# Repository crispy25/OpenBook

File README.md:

# OpenBook - TSC Project
### Author: Popescu Cristian-Emanuel 332CA

## Diagram

## Hardware functionality

+ ESP32-C6 MCU
    - Manages all peripherals, including the display, sensors, buttons, and USB-C interface.
    - Interfaces: SPI, I2C, USB, UART, Wi-Fi

+ Power Supply - CELLEVIA BATTERIES LP584174
    - The 1800mAh Polymer Lithium-Ion battery is connected to the charging IC.
    - A single LDO generates the required single 3.3V power rail for the entire board, powering the ESP32, sensors and other components.

+ Battery management - MAX17048G+T10
    - The battery management module is using the I2C interface to communicate with the battery fuel gauge IC.
    - The charging IC is controlled via GPIO pins.

+ Display Interface - Waveshare WSH-13187 7.5" e-Paper display 
    - The 800x480 resolution display is connected to the ESP32-C6 via a 4-wire SPI interface.
    - Dedicated CS, DC, RST, and BUSY pins are used for control.

+ Sensor - Bosch BME680
    - Measures temperature, humidity, pressure and air quality.
    - The BME680 sensor is connected to the ESP32-C6 via an I2C bus.
    - Pull-up resistors are used on the I2C lines.

+ RTC - DS3231
    - Real Time Clock with supercapacitor back-up.
    - Connected via I2C interface.

+ User Interface
    - The three tactile buttons are connected to GPIO pins on the ESP32-C6.
    - Hardware debouncing circuitry is implemented using RC filters.
    - The RESET button restarts the device, typically used to recover from unresponsive states or system errors.
    - The BOOT button allows the user to start up the device.
    - The CHANGE button lets the user scroll or cycle through menus and book selections.

+ External NOR Flash 64MB - W25Q512JVEIQ
    - Non-Volatile flash memory that provides a storage solution.
    - Interface: SPI

+ USB-C Interface
    - The USB-C connector is connected to the ESP32-C6's USB interface.
    - A dedicated ESD protection IC is used on the data and power lines.
    - Proper termination resistors are used for USB-C implementation.

+ SD Memory Card Connector - Attend Tech 112A-TAAR-R03
    - Interface: SPI

+ Qwiic / Stemma QT
    - Plug-and-play I2C connection system for easy expansion of peripheral modules.

## Power management and consumption

| Mode       | ESP32  | EPD  | BME680    | DS3231  | MAX17048 | SD Card | Total Current | Runtime       |
|------------|--------|------|-----------|---------|----------|---------|---------------|:-------------:|
| Active     | 100mA  | 30mA | 2mA       | 0.2mA   | 0.05mA   | 80mA    | ~212 mA       | ~8.5 hours    |
| Idle       | 50mA   | 1µA  | 150µA     | 0.2mA   | 0.05mA   | 2mA     | ~52.4 mA      | ~1.4 days     |
| Deep Sleep | 0.15mA | 1µA  | 0.00015mA | 0.003mA | 0.001mA  | 0.1mA   | ~0.255 mA     | ~9.7 months   |

## ESP32-C6 Pin description

+ EN -> Resets the MCU
+ IO0 - INT_RTC -> Used to receive interrupts signals from RTC, allowing for two major functionalities: Alarm and Square Wave Output
+ IO1 - 32KHz -> Used for a stable clock signal of 32.768 kHz generated by the RTC
+ IO2 – MISO -> Master In Slave Out Signal, used in the SPI communication with the SD Card
+ IO3 - EPD_BUSY -> Indicates display driver status
+ IO4 – SS_SD -> Chip select for SPI communication with SD Card
+ IO5 – EPD_DC -> Display serial communication Command/Data input
+ IO6 – SCK -> Clock signal for I2C communication
+ IO7 – MOSI -> Master Out Slave In Signal, used to send data to display and SD Card
+ IO8 - GPIO8 - Controls MCU boot mode
+ IO9 - IO/BOOT -> Used to detect BOOT button press
+ NC -> Not connected
+ 3V3 -> Used to power the MCU and the other components
+ IO10 - EPD_CS -> Chip select for SPI serial communication with the display
+ IO11 - FLASH_CS -> Chip select for SPI communication with the flash
+ IO12 - USB_D- -> Used in USB differential communication
+ IO13 - USB_D+ -> Used in USB differential communication
+ IO15 - IO/CHANGE -> Used to detect CHANGE button press
+ TXD0/GPIO16 - TX -> Sends data to another device via UART
+ RXD0/GPIO17 - RX -> Receives data from another device via UART
+ IO18 - RTC_RST -> Resets the RTC
+ IO19 - I2C_PW -> Power source for I2C components
+ IO20 - EPD_3V3_C -> Display IO voltage supply
+ IO21 - SDA -> Used to send and receive data in the I2C communication with the sensor, RTC module and Battery Fuel Gauge
+ IO22 - SCL -> Clock signal for I2C communication
+ IO23 - EPD_RST -> Global reset signal for the display
+ GND -> Shared Voltage Reference

## Bill of Materials:
|                                                                                                         |                                                                                |     |                                                                                                                                                                                                                                                                                                                                                                                                                                                                                                                                                                                                                  |                                                                                                                                                                                                                |
| ------------------------------------------------------------------------------------------------------- | ------------------------------------------------------------------------------ | --- | ---------------------------------------------------------------------------------------------------------------------------------------------------------------------------------------------------------------------------------------------------------------------------------------------------------------------------------------------------------------------------------------------------------------------------------------------------------------------------------------------------------------------------------------------------------------------------------------------------------------- | -------------------------------------------------------------------------------------------------------------------------------------------------------------------------------------------------------------- |
| Parts                                                                                                   | Value                                                                          | Qty | CHECK_PRICES                                                                                                                                                                                                                                                                                                                                                                                                                                                                                                                                                                                                     | DATASHEET                                                                                                                                                                                                      |
| CHG_LED                                                                                                 |                                                                                | 1   | [https://ro.mouser.com/ProductDetail/ams-OSRAM/KO-EELP41.22-Q1S2-25-A8J8-020-R18?qs=ZcfC38r4PoswH9uD%2FZTNyw%3D%3D](https://ro.mouser.com/ProductDetail/ams-OSRAM/KO-EELP41.22-Q1S2-25-A8J8-020-R18?qs=ZcfC38r4PoswH9uD%2FZTNyw%3D%3D)                                                                                                                                                                                                                                                                                                                                                                           | [https://www.farnell.com/datasheets/4386964.pdf](https://www.farnell.com/datasheets/4386964.pdf)                                                                                                               |
| SJ1                                                                                                     |                                                                                | 1   | [https://ro.mouser.com/ProductDetail/ROHM-Semiconductor/PMR01ZZPJ000?qs=jQ44l%2F%2F3jsmEdW2XxNXnVw%3D%3D](https://ro.mouser.com/ProductDetail/ROHM-Semiconductor/PMR01ZZPJ000?qs=jQ44l%2F%2F3jsmEdW2XxNXnVw%3D%3D)                                                                                                                                                                                                                                                                                                                                                                                               | [https://fscdn.rohm.com/en/products/databook/datasheet/passive/resistor/chip_resistor/pmr_series-e.pdf](https://fscdn.rohm.com/en/products/databook/datasheet/passive/resistor/chip_resistor/pmr_series-e.pdf) |
| C7                                                                                                      | 10uF                                                                          | 1   | [https://ro.mouser.com/ProductDetail/KYOCERA-AVX/CM05X5R106M10AH?qs=MyNHzdoqoQKSCgSEDR5Ylg%3D%3D](https://ro.mouser.com/ProductDetail/KYOCERA-AVX/CM05X5R106M10AH?qs=MyNHzdoqoQKSCgSEDR5Ylg%3D%3D)                                                                                                                                                                                                                                                                                                                                                                                                               | [https://ro.mouser.com/datasheet/2/40/CM_Series_e-2835982.pdf](https://ro.mouser.com/datasheet/2/40/CM_Series_e-2835982.pdf)                                                                                   |
| EPD_C5                                                                                                  | 0.1uF/50V                                                                      | 1   | [04025C104JAT2A KYOCERA AVX \| Mouser Romania](https://ro.mouser.com/ProductDetail/KYOCERA-AVX/04025C104JAT2A?qs=yqaQSyyJnNjAUYBPnTRwrw%3D%3D)                                                                                                                                                                                                                                                                                                                                                                                                                                                                   | [https://ro.mouser.com/datasheet/2/40/AutoMLCC-2952695.pdf](https://ro.mouser.com/datasheet/2/40/AutoMLCC-2952695.pdf)                                                                                         |
| R3                                                                                                      | 0.47                                                                           | 1   | [https://ro.mouser.com/ProductDetail/Vishay-Dale/RCWE0402R470FKEA?qs=sGAEpiMZZMvdGkrng054t3yNvgEjAsaw5ZqUmX9fhQU%3D](https://ro.mouser.com/ProductDetail/Vishay-Dale/RCWE0402R470FKEA?qs=sGAEpiMZZMvdGkrng054t3yNvgEjAsaw5ZqUmX9fhQU%3D)                                                                                                                                                                                                                                                                                                                                                                         | [rcwe.pdf](https://www.vishay.com/docs/20019/rcwe.pdf)                                                                                                                                                         |
| R1_PWRUSB                                                                                               | 100K                                                                           | 1   | [MCS0402MD1003BE000 Vishay / Beyschlag \| Mouser Romania](https://ro.mouser.com/ProductDetail/Vishay-Beyschlag/MCS0402MD1003BE000?qs=sGAEpiMZZMvdGkrng054t2cqbZCzJY7NbpFPWPjr8LU6rj01EMMGYg%3D%3D)                                                                                                                                                                                                                                                                                                                                                                                                               | [mcs0402at-mct0603at-mcu0805at-mca1206at.pdf](https://www.vishay.com/docs/28952/mcs0402at-mct0603at-mcu0805at-mca1206at.pdf)                                                                                   |
| C1, C2, C4_USB, C6, C8, C9, C10, C_DELAY                                                                | 100nF                                                                          | 8   | [0402YC104MAT2A KYOCERA AVX \| Mouser Romania](https://ro.mouser.com/ProductDetail/KYOCERA-AVX/0402YC104MAT2A?qs=O2%2FeDh0sX9yiCaLwpXy1bw%3D%3D)                                                                                                                                                                                                                                                                                                                                                                                                                                                                 | [https://ro.mouser.com/datasheet/2/40/KGM_X7R-3223212.pdf](https://ro.mouser.com/datasheet/2/40/KGM_X7R-3223212.pdf)                                                                                           |
| C3                                                                                                      | 100uF                                                                          | 1   | [F910J107MBAAJ6 KYOCERA AVX \| Mouser Romania](https://ro.mouser.com/ProductDetail/KYOCERA-AVX/F910J107MBAAJ6?qs=PqoDHHvF649LraCA%2FjeGXg%3D%3D)                                                                                                                                                                                                                                                                                                                                                                                                                                                                 | https://ro.mouser.com/datasheet/2/40/F91_AJ6-3162641.pdf                                                                                                                                                       |
| R1, R1_PINH, R1_PINH1, R2-PINH, R2-PINH1, R4, R5, R6, R7, R8, R9, R10, R_BOOT, R_CHANGE, R_CL1, R_RESET | 10K                                                                            | 16  | [CRCW040210K0FKEDC Vishay / Dale \| Mouser Romania](https://ro.mouser.com/ProductDetail/Vishay-Dale/CRCW040210K0FKEDC?qs=sGAEpiMZZMvdGkrng054t0DrEhLhGh8ghRTPC4LoFoV0V5heIyAs3Q%3D%3D)                                                                                                                                                                                                                                                                                                                                                                                                                           | [crcwce3.pdf](https://www.vishay.com/docs/28773/crcwce3.pdf)                                                                                                                                                   |
| J4                                                                                                      | 112A-TAAR-R03_ATTEND                                                           | 1   | [https://store.comet.srl.ro/Catalogue/Product/43497/](https://store.comet.srl.ro/Catalogue/Product/43497/)                                                                                                                                                                                                                                                                                                                                                                                                                                                                                                       | [https://www.attend.com.tw/data/download/file/112A-TAAR-R03_Spec.pdf](https://www.attend.com.tw/data/download/file/112A-TAAR-R03_Spec.pdf)                                                                     |
| R_CAPACITOR                                                                                             | 15                                                                             | 1   | [https://ro.mouser.com/ProductDetail/Vishay-Dale/CRCW040215R0FKEDC?qs=sGAEpiMZZMvdGkrng054t0DrEhLhGh8gIyCo%252BhYIiOaNlcXwcpoKSQ%3D%3D](https://ro.mouser.com/ProductDetail/Vishay-Dale/CRCW040215R0FKEDC?qs=sGAEpiMZZMvdGkrng054t0DrEhLhGh8gIyCo%252BhYIiOaNlcXwcpoKSQ%3D%3D)                                                                                                                                                                                                                                                                                                                                   | [crcwce3.pdf](https://www.vishay.com/docs/28773/crcwce3.pdf)                                                                                                                                                   |
| C5                                                                                                      | 1uF                                                                            | 1   | [0402YC104MAT2A KYOCERA AVX \| Mouser Romania](https://ro.mouser.com/ProductDetail/KYOCERA-AVX/0402YC104MAT2A?qs=O2%2FeDh0sX9yiCaLwpXy1bw%3D%3D)                                                                                                                                                                                                                                                                                                                                                                                                                                                                 | [https://ro.mouser.com/datasheet/2/40/KGM_X7R-3223212.pdf](https://ro.mouser.com/datasheet/2/40/KGM_X7R-3223212.pdf)                                                                                           |
| EPD_C1, EPD_C2, EPD_C6, EPD_C7, EPD_C8, EPD_C9, EPD_C10, EPD_C11, EPD_C12                               | 1uF/50V                                                                        | 9   | [GRM155R61H105KE05D Murata Electronics \| Mouser Romania](https://ro.mouser.com/ProductDetail/Murata-Electronics/GRM155R61H105KE05D?qs=d0WKAl%252BL4KazJ%252BOnevMfYg%3D%3D)                                                                                                                                                                                                                                                                                                                                                                                                                                     | [GRM155R61H105KE05_01A-1983895.pdf](https://ro.mouser.com/datasheet/2/281/1/GRM155R61H105KE05_01A-1983895.pdf)                                                                                                 |
| R2                                                                                                      | 2.2                                                                            | 1   | [CRCW04022R20JNEDHP Vishay / Dale \| Mouser Romania](https://ro.mouser.com/ProductDetail/Vishay-Dale/CRCW04022R20JNEDHP?qs=sGAEpiMZZMvdGkrng054tyhjHjtogURyZ4iA06yjwtU%3D)                                                                                                                                                                                                                                                                                                                                                                                                                                       | [https://www.vishay.com/docs/20043/crcwhpe3.pdf](https://www.vishay.com/docs/20043/crcwhpe3.pdf)                                                                                                               |
| R1_BAT                                                                                                  | 200                                                                            | 1   | [CRCW0402200RJNEDHP Vishay / Dale \| Mouser Romania](https://ro.mouser.com/ProductDetail/Vishay-Dale/CRCW0402200RJNEDHP?qs=sGAEpiMZZMvdGkrng054t7z4BkURc4Lz9xM5ulmOcXZJ7C0YzNP%252BSg%3D%3D)                                                                                                                                                                                                                                                                                                                                                                                                                     | [crcwhpe3.pdf](https://www.vishay.com/docs/20043/crcwhpe3.pdf)                                                                                                                                                 |
| Q1, Q2                                                                                                  | 20V/4.2A/52mO/1.4W                                                             | 2   | [https://ro.mouser.com/ProductDetail/Diodes-Incorporated/DMG2305UX-7?qs=L1DZKBg7t5F%2FNBHrjfxC%252Bg%3D%3D](https://ro.mouser.com/ProductDetail/Diodes-Incorporated/DMG2305UX-7?qs=L1DZKBg7t5F%2FNBHrjfxC%252Bg%3D%3D)                                                                                                                                                                                                                                                                                                                                                                                           | [DMG2305UX](https://www.diodes.com/assets/Datasheets/DMG2305UX.pdf)                                                                                                                                            |
| R2_BAT                                                                                                  | 2K                                                                             | 1   | [MCS0402PD2001DE500 Vishay / Beyschlag \| Mouser Romania](https://ro.mouser.com/ProductDetail/Vishay-Beyschlag/MCS0402PD2001DE500?qs=sGAEpiMZZMvdGkrng054t7z4BkURc4Lz%2FlDTCWzmnHsTHTkVY59%252BKw%3D%3D)                                                                                                                                                                                                                                                                                                                                                                                                         | [https://www.vishay.com/docs/28916/mcxhp.pdf](https://www.vishay.com/docs/28916/mcxhp.pdf)                                                                                                                     |
| C1_BAT, C1_BAT1, C1_BAT2, C2_BAT, C5_USB                                                                | 4.7uF                                                                          | 5   | [CM05X5R475M25AH KYOCERA AVX \| Mouser Romania](https://ro.mouser.com/ProductDetail/KYOCERA-AVX/CM05X5R475M25AH?qs=MyNHzdoqoQJvFdZaEuclBg%3D%3D)                                                                                                                                                                                                                                                                                                                                                                                                                                                                 | https://ro.mouser.com/datasheet/2/40/CM_Series_e-2835982.pdf                                                                                                                                                   |
| C4                                                                                                      | 4.7uF/25V                                                                      | 1   | [CM05X5R475M25AH KYOCERA AVX \| Mouser Romania](https://ro.mouser.com/ProductDetail/KYOCERA-AVX/CM05X5R475M25AH?qs=MyNHzdoqoQJvFdZaEuclBg%3D%3D)                                                                                                                                                                                                                                                                                                                                                                                                                                                                 | https://ro.mouser.com/datasheet/2/40/CM_Series_e-2835982.pdf                                                                                                                                                   |
| R2-USB, R2-USB1                                                                                         | 5k1                                                                            | 2   | [https://ro.mouser.com/ProductDetail/Vishay-Beyschlag/MCS04020C5101FE000?qs=sGAEpiMZZMvdGkrng054t4QdAY%2FQ0LweI%252Blr2dxb1tw%3D](https://ro.mouser.com/ProductDetail/Vishay-Beyschlag/MCS04020C5101FE000?qs=sGAEpiMZZMvdGkrng054t4QdAY%2FQ0LweI%252Blr2dxb1tw%3D)                                                                                                                                                                                                                                                                                                                                               | [mcx0x0xpro.pdf](https://www.vishay.com/docs/28705/mcx0x0xpro.pdf)                                                                                                                                             |
| L1                                                                                                      | 68uH                                                                           | 1   | [https://ro.mouser.com/ProductDetail/Wurth-Elektronik/744043680?qs=PGXP4M47uW6VkZq%252BkzjrHA%3D%3D](https://ro.mouser.com/ProductDetail/Wurth-Elektronik/744043680?qs=PGXP4M47uW6VkZq%252BkzjrHA%3D%3D)                                                                                                                                                                                                                                                                                                                                                                                                         | [744043680 Datasheet WE-TPC SMT Shielded Tiny Power Inductor](https://www.we-online.com/components/products/datasheet/744043680.pdf)                                                                           |
| IC1                                                                                                     | BD5229G-TR                                                                     | 1   | [https://ro.mouser.com/ProductDetail/ROHM-Semiconductor/BD5229G-TR?qs=4kLU8WoGk0vvnhrrYwdszw%3D%3D](https://ro.mouser.com/ProductDetail/ROHM-Semiconductor/BD5229G-TR?qs=4kLU8WoGk0vvnhrrYwdszw%3D%3D)                                                                                                                                                                                                                                                                                                                                                                                                           | [BD52xx Series / BD53xx Series : Power Management](https://fscdn.rohm.com/en/products/databook/datasheet/ic/power/voltage_detector/bd52xxg-e.pdf)                                                              |
| BOOT_BUTTON, CHANGE_BUTTON, RESET_BUTTON                                                                | BUTTON_CUSYOMV1                                                                | 3   | [https://ro.mouser.com/ProductDetail/Panasonic/EVQ-P7L01P?qs=rJ%252BziJWpyszWhhNszc02jQ%3D%3D](https://ro.mouser.com/ProductDetail/Panasonic/EVQ-P7L01P?qs=rJ%252BziJWpyszWhhNszc02jQ%3D%3D)                                                                                                                                                                                                                                                                                                                                                                                                                     | [https://api.pim.na.industrial.panasonic.com/file_stream/main/fileversion/245500](https://api.pim.na.industrial.panasonic.com/file_stream/main/fileversion/245500)                                             |
| C10_SUPERCAP                                                                                            | CPH3225A                                                                       | 1   | [https://ro.mouser.com/ProductDetail/Seiko-Semiconductors/CPH3225A?qs=3etwrb1wR%252BhUOph6lAO7eg%3D%3D](https://ro.mouser.com/ProductDetail/Seiko-Semiconductors/CPH3225A?qs=3etwrb1wR%252BhUOph6lAO7eg%3D%3D)                                                                                                                                                                                                                                                                                                                                                                                                   | [https://ro.mouser.com/datasheet/2/360/Seiko_Instruments_MicroBattery_E_20230330_2024Jan_-3561061.pdf](https://ro.mouser.com/datasheet/2/360/Seiko_Instruments_MicroBattery_E_20230330_2024Jan_-3561061.pdf)   |
| U3                                                                                                      | DS3231SN#                                                                      | 1   | [https://ro.mouser.com/ProductDetail/Analog-Devices-Maxim-Integrated/DS3231SN?qs=1eQvB6Dk1vhUlr8%2FOrV0Fw%3D%3D](https://ro.mouser.com/ProductDetail/Analog-Devices-Maxim-Integrated/DS3231SN?qs=1eQvB6Dk1vhUlr8%2FOrV0Fw%3D%3D)                                                                                                                                                                                                                                                                                                                                                                                 | [DS3231-3421123.pdf](https://ro.mouser.com/datasheet/2/609/DS3231-3421123.pdf)                                                                                                                                 |
| U2                                                                                                      | ESP32-C6-WROOM-1-N8                                                            | 1   | [https://ro.mouser.com/ProductDetail/Espressif-Systems/ESP32-C6-WROOM-1-N8?qs=8Wlm6%252BaMh8ST02Gmwp74cw%3D%3D](https://ro.mouser.com/ProductDetail/Espressif-Systems/ESP32-C6-WROOM-1-N8?qs=8Wlm6%252BaMh8ST02Gmwp74cw%3D%3D)                                                                                                                                                                                                                                                                                                                                                                                   | [Espressif_ESP32_C6_WROOM_1__Datasheet_V0_1_PRELIMI-3239987.pdf](https://ro.mouser.com/datasheet/2/891/Espressif_ESP32_C6_WROOM_1__Datasheet_V0_1_PRELIMI-3239987.pdf)                                         |
| PFMF.050.1                                                                                              | ESP32C6_VARISTORCN1812                                                         | 1   | [https://ro.mouser.com/ProductDetail/Bourns/BVR1812-04R?qs=mELouGlnn3dev%2FRLzuGBiQ%3D%3D](https://ro.mouser.com/ProductDetail/Bourns/BVR1812-04R?qs=mELouGlnn3dev%2FRLzuGBiQ%3D%3D)                                                                                                                                                                                                                                                                                                                                                                                                                             | [BVR1812 SMD Series Low Voltage Varistors](https://ro.mouser.com/datasheet/2/54/Bourns_12_20_2023_BVR1812_Datasheet-3386163.pdf)                                                                               |
| D2, D7                                                                                                  | ESP32_WROVER_AVX---SD0805S020S1R0_AVX_SD0805S020S1R0_0_0AVX_SD0805S020S1R0_0_0 | 2   | [SD0805S020S1R0 KYOCERA AVX \| Mouser Romania](https://ro.mouser.com/ProductDetail/KYOCERA-AVX/SD0805S020S1R0?qs=jCA%252BPfw4LHbpkAoSnwrdjw%3D%3D)                                                                                                                                                                                                                                                                                                                                                                                                                                                               | [https://ro.mouser.com/datasheet/2/40/schottky-3165252.pdf](https://ro.mouser.com/datasheet/2/40/schottky-3165252.pdf)                                                                                         |
| SENSOR2                                                                                                 | ESP32_WROVER_BME680_BME680                                                     | 1   | [https://ro.mouser.com/ProductDetail/Bosch-Sensortec/BME680?qs=v271MhAjFHjo0yA%2FC4OnDQ%3D%3D](https://ro.mouser.com/ProductDetail/Bosch-Sensortec/BME680?qs=v271MhAjFHjo0yA%2FC4OnDQ%3D%3D)                                                                                                                                                                                                                                                                                                                                                                                                                     | [https://ro.mouser.com/datasheet/2/783/BST_BME680_DS001-1509608.pdf](https://ro.mouser.com/datasheet/2/783/BST_BME680_DS001-1509608.pdf)                                                                       |
| MCP73831                                                                                                | ESP32_WROVER_SPARKFUN-IC-POWER_MCP73831                                        | 1   | [https://ro.mouser.com/ProductDetail/Microchip-Technology/MCP73831T-2ACI-OT?qs=yUQqVecv4qvbBQBGbHx0Mw%3D%3D](https://ro.mouser.com/ProductDetail/Microchip-Technology/MCP73831T-2ACI-OT?qs=yUQqVecv4qvbBQBGbHx0Mw%3D%3D)                                                                                                                                                                                                                                                                                                                                                                                         | [MCP73831/MCP73832 Data Sheet](https://ro.mouser.com/datasheet/2/268/MCP73831_Family_Data_Sheet_DS20001984H-3441711.pdf)                                                                                       |
| J1                                                                                                      | FH34SRJ-24S-0.5SH_99_                                                          | 1   | [FH34SRJ-24S-0.5SH(99) Hirose Connector \| Mouser Romania](https://ro.mouser.com/ProductDetail/Hirose-Connector/FH34SRJ-24S-0.5SH99?qs=vcbW%252B4%252BSTIpKBl5ap9J8Fw%3D%3D)                                                                                                                                                                                                                                                                                                                                                                                                                                     | [https://ro.mouser.com/datasheet/2/185/FH34SRJ_24S_0_5SH_99__CL0580_1255_6_99_2DDrawing_0-1615044.pdf](https://ro.mouser.com/datasheet/2/185/FH34SRJ_24S_0_5SH_99__CL0580_1255_6_99_2DDrawing_0-1615044.pdf)   |
| U4                                                                                                      | MAX17048G+T10                                                                  | 1   | [MAX17048G+T10 Analog Devices / Maxim Integrated \| Mouser Romania](https://ro.mouser.com/ProductDetail/Analog-Devices-Maxim-Integrated/MAX17048G%2bT10?qs=D7PJwyCwLAoGnnn8jEPRBQ%3D%3D)                                                                                                                                                                                                                                                                                                                                                                                                                         | [MAX17048_MAX17049-3469099.pdf](https://ro.mouser.com/datasheet/2/609/MAX17048_MAX17049-3469099.pdf)                                                                                                           |
| D3, D4, D5                                                                                              | MBR0530                                                                        | 3   | [https://ro.mouser.com/ProductDetail/onsemi/MBR0530T1G?qs=3JMERSakeboS%2FFOxJUMWeg%3D%3D](https://ro.mouser.com/ProductDetail/onsemi/MBR0530T1G?qs=3JMERSakeboS%2FFOxJUMWeg%3D%3D)                                                                                                                                                                                                                                                                                                                                                                                                                               | [MBR0530T1 - Surface Mount Schottky Power Rectifier](https://www.onsemi.com/download/data-sheet/pdf/mbr0530t1-d.pdf)                                                                                           |
| D6, D8, D9, D10, D11, D12                                                                               | PGB1010603MR                                                                   | 6   | [PGB1010603MR Littelfuse \| Mouser Romania](https://ro.mouser.com/ProductDetail/Littelfuse/PGB1010603MR?qs=gu7KAQ731URLg4GSnNNN7Q%3D%3D)                                                                                                                                                                                                                                                                                                                                                                                                                                                                         | [pulseguard-esd-suppressors-pgb1-datasheet](https://www.littelfuse.com/assetdocs/pulseguard-esd-suppressors-pgb1-datasheet?assetguid=8a337998-d54d-466b-be4e-dc5bcd1f9321)                                     |
| J3                                                                                                      | QWIIC_RIGHT_ANGLE                                                              | 1   | [https://ro.mouser.com/ProductDetail/SparkFun/PRT-14417?qs=wd5RIQLrsJhgdz%2FpmZ%2F3GQ%3D%3D](https://ro.mouser.com/ProductDetail/SparkFun/PRT-14417?qs=wd5RIQLrsJhgdz%2FpmZ%2F3GQ%3D%3D)                                                                                                                                                                                                                                                                                                                                                                                                                         | [eSH.doc](https://ro.mouser.com/datasheet/2/813/Qwiic_Connector_Datasheet-1223982.pdf)                                                                                                                         |
| J2                                                                                                      | SAMACSYS_PARTS_USB4110-GF-A                                                    | 1   | [USB4110-GF-A GCT \| Mouser Romania](https://ro.mouser.com/ProductDetail/GCT/USB4110-GF-A?qs=KUoIvG%2F9IlYiZvIXQjyJeA%3D%3D)                                                                                                                                                                                                                                                                                                                                                                                                                                                                                     | [https://ro.mouser.com/datasheet/2/837/GCT_USB4110_Product_Drawing___20k_cycles-3455479.pdf](https://ro.mouser.com/datasheet/2/837/GCT_USB4110_Product_Drawing___20k_cycles-3455479.pdf)                       |
| Q3                                                                                                      | SI1308EDL-T1-GE3                                                               | 1   | [SI1308EDL-T1-GE3 Vishay Semiconductors \| Mouser Romania](https://ro.mouser.com/ProductDetail/Vishay-Semiconductors/SI1308EDL-T1-GE3?qs=bX1%252BNvsK%2FBramh9tgpOaEw%3D%3D)                                                                                                                                                                                                                                                                                                                                                                                                                                     | [si1308edl.pdf](https://www.vishay.com/docs/63399/si1308edl.pdf)                                                                                                                                               |
| TP1, TP2, TP3, TP4, TP5, TP6, TP7, TP8, TP9, TP10, TP11, TP12, TP13, TP14, TP15, TP16, TP17             | TPTP20R                                                                        | 17  | \-                                                                                                                                                                                                                                                                                                                                                                                                                                                                                                                                                                                                               | \-                                                                                                                                                                                                             |
| D1                                                                                                      | USBLC6-2SC6Y                                                                   | 1   | [https://ro.mouser.com/ProductDetail/STMicroelectronics/USBLC6-2SC6Y?qs=gNDSiZmRJS%2FOgDexvXkdow%3D%3D&utm_id=6470900573&utm_source=google&utm_medium=cpc&utm_marketing_tactic=emeacorp&gad_source=1&gclid=Cj0KCQjwtJ6_BhDWARIsAGanmKe24j6YW-hEX9oCZjA_HBeoOu39IdVcWjE3FJxSOq0SkXe959vSFcwaArhpEALw_wcB](https://ro.mouser.com/ProductDetail/STMicroelectronics/USBLC6-2SC6Y?qs=gNDSiZmRJS%2FOgDexvXkdow%3D%3D&utm_id=6470900573&utm_source=google&utm_medium=cpc&utm_marketing_tactic=emeacorp&gad_source=1&gclid=Cj0KCQjwtJ6_BhDWARIsAGanmKe24j6YW-hEX9oCZjA_HBeoOu39IdVcWjE3FJxSOq0SkXe959vSFcwaArhpEALw_wcB) | https://ro.mouser.com/datasheet/2/389/usblc6_2sc6y-1852505.pdf                                                                                                                                                 |
| U1                                                                                                      | W25Q512JVEIQ                                                                   | 1   | [https://ro.mouser.com/ProductDetail/Winbond/W25Q512JVEIQ?qs=l7cgNqFNU1jw6svr3at6tA%3D%3D](https://ro.mouser.com/ProductDetail/Winbond/W25Q512JVEIQ?qs=l7cgNqFNU1jw6svr3at6tA%3D%3D)                                                                                                                                                                                                                                                                                                                                                                                                                             | [Winbond_W25Q512JV_Datasheet-3240039.pdf](https://ro.mouser.com/datasheet/2/949/Winbond_W25Q512JV_Datasheet-3240039.pdf)                                                                                       |
| IC4                                                                                                     | XC6220A331MR-G                                                                 | 1   | [https://ro.mouser.com/ProductDetail/Torex-Semiconductor/XC6220A331MR-G?qs=AsjdqWjXhJ8ZSWznL1J0gg%3D%3D](https://ro.mouser.com/ProductDetail/Torex-Semiconductor/XC6220A331MR-G?qs=AsjdqWjXhJ8ZSWznL1J0gg%3D%3D)                                                                                                                                                                                                                                                                                                                                                                                                 | [xc6220-3371556.pdf](https://ro.mouser.com/datasheet/2/760/xc6220-3371556.pdf)                                                                                                                                 |

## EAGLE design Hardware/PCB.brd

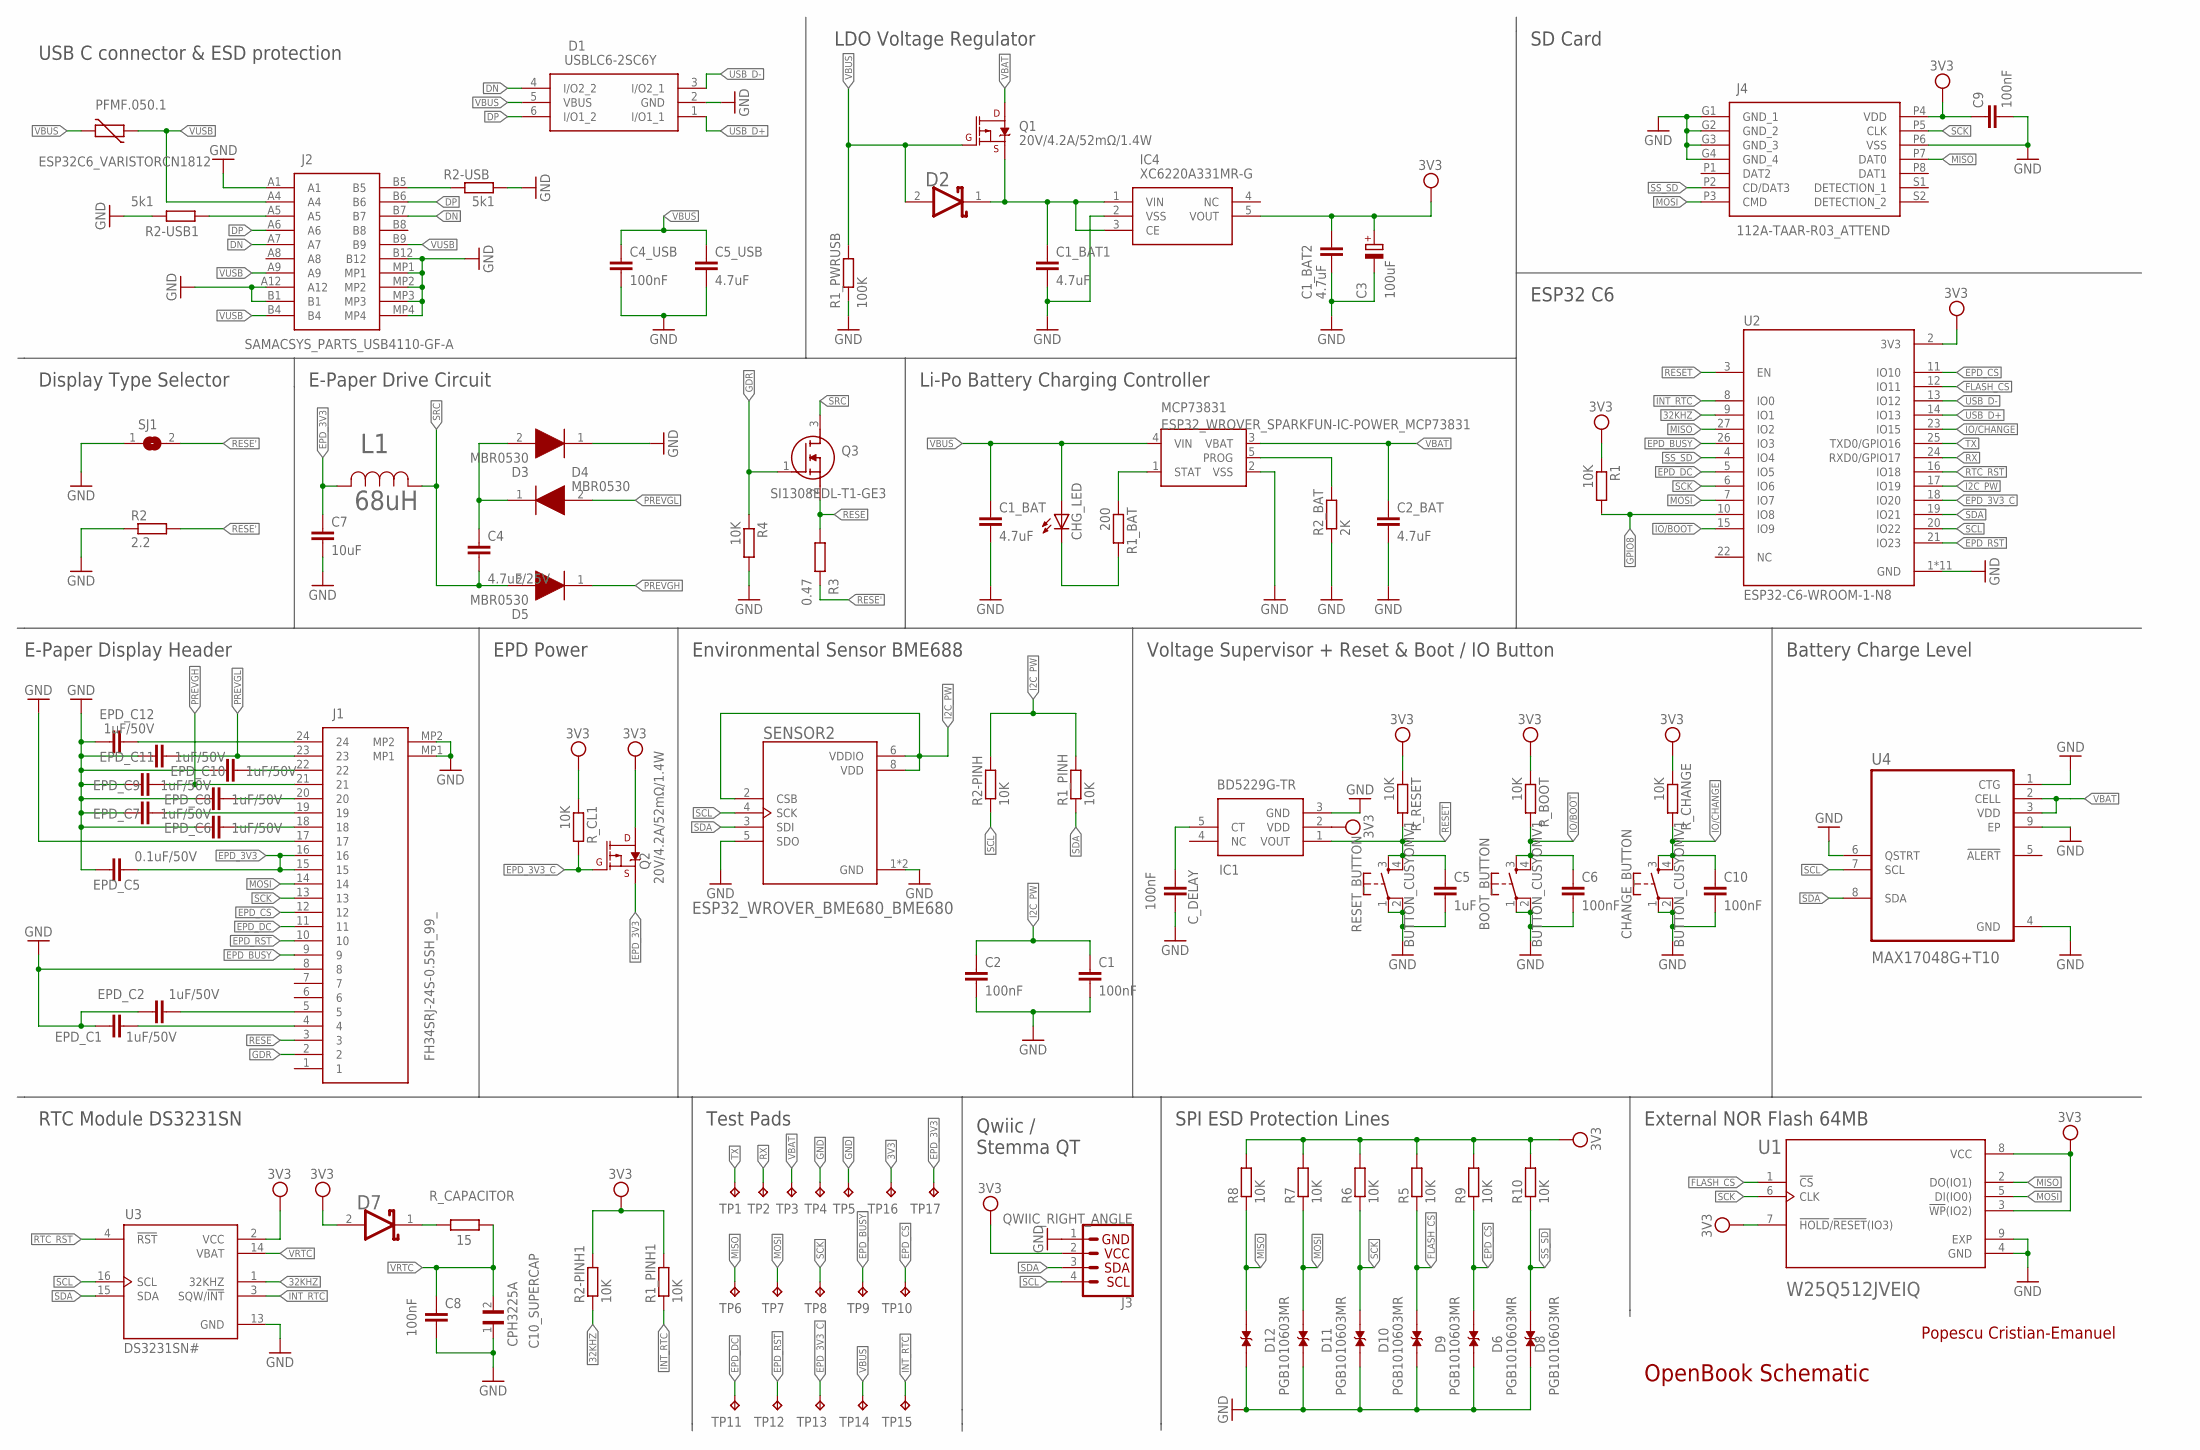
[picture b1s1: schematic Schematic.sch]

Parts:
BOOT_BUTTON: BUTTON_CUSYOMV1; MYBUTTON
C1, C2, C4_USB, C6, C8, C9, C10: 100nF; ESP32_WROVER_EAGLE-LTSPICE_C0402
C1_BAT, C1_BAT1, C1_BAT2, C2_BAT, C5_USB: 4.7uF; ESP32_WROVER_EAGLE-LTSPICE_C0402
C3: 100uF; RCL_CT3528
C4: 4.7uF/25V; ESP32_WROVER_EAGLE-LTSPICE_C0402
C5: 1uF; ESP32_WROVER_EAGLE-LTSPICE_C0402
C7: 10uF; ESP32_WROVER_EAGLE-LTSPICE_C0402
C10_SUPERCAP: CPH3225A; CAPCP3225X100N
CHANGE_BUTTON: BUTTON_CUSYOMV1; MYBUTTON
CHG_LED: ADAFRUIT_LEDCHIP-LED0603; ADAFRUIT_CHIP-LED0603
C_DELAY: 100nF; ESP32_WROVER_EAGLE-LTSPICE_C0402
D1: USBLC6-2SC6Y; SOT95P280X145-6N
D2, D7: ESP32_WROVER_AVX---SD0805S020S1R0_AVX_SD0805S020S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; ESP32_WROVER_AVX---SD0805S020S1R0_AVX_SD0805S020S1R0_0
D3, D4, D5: MBR0530; SOD3716X135N
D6, D8, D9, D10, D11, D12: PGB1010603MR; DIOC1608X36N
EPD_C1, EPD_C2, EPD_C6, EPD_C7, EPD_C8, EPD_C9, EPD_C10, EPD_C11, EPD_C12: 1uF/50V; ESP32_WROVER_EAGLE-LTSPICE_C0402
EPD_C5: 0.1uF/50V; ESP32_WROVER_EAGLE-LTSPICE_C0402
IC1: BD5229G-TR; SOT95P280X125-5N
IC4: XC6220A331MR-G; SOT95P280X120-5N
J1: FH34SRJ-24S-0.5SH_99_; FH34SRJ24S05SH99
J2: SAMACSYS_PARTS_USB4110-GF-A; SAMACSYS_PARTS_USB4110GFA
J3: QWIIC_RIGHT_ANGLE; JST04_1MM_RA
J4: 112A-TAAR-R03_ATTEND; 112ATAARR03ATTEND
L1: 68uH; IND_4828-WE-TPC_WRE
MCP73831: ESP32_WROVER_SPARKFUN-IC-POWER_MCP73831; ESP32_WROVER_SPARKFUN-IC-POWER_SOT23-5
PFMF.050.1: ESP32C6_VARISTORCN1812; ESP32C6_VARISTOR_CT/CN1812
Q1, Q2: 20V/4.2A/52mΩ/1.4W; ESP32_WROVER_SPARKFUN-DISCRETESEMI_SOT23-3
Q3: SI1308EDL-T1-GE3; SOT65P210X110-3N
R1, R1_PINH, R1_PINH1, R2-PINH, R2-PINH1, R4, R5, R6, R7, R8, R9, R10: 10K; ESP32_WROVER_EAGLE-LTSPICE_R0402
R1_BAT: 200; ESP32_WROVER_EAGLE-LTSPICE_R0402
R1_PWRUSB: 100K; ESP32_WROVER_EAGLE-LTSPICE_R0402
R2: 2.2; ESP32_WROVER_EAGLE-LTSPICE_R0402
R2-USB, R2-USB1: 5k1; ESP32_WROVER_EAGLE-LTSPICE_R0402
R2_BAT: 2K; ESP32_WROVER_EAGLE-LTSPICE_R0402
R3: 0.47; ESP32_WROVER_EAGLE-LTSPICE_R0402
RESET_BUTTON: BUTTON_CUSYOMV1; MYBUTTON
R_BOOT: 10K; ESP32_WROVER_EAGLE-LTSPICE_R0402
R_CAPACITOR: 15; ESP32_WROVER_EAGLE-LTSPICE_R0402
R_CHANGE: 10K; ESP32_WROVER_EAGLE-LTSPICE_R0402
R_CL1: 10K; ESP32_WROVER_EAGLE-LTSPICE_R0402
R_RESET: 10K; ESP32_WROVER_EAGLE-LTSPICE_R0402
SENSOR2: ESP32_WROVER_BME680_BME680; ESP32_WROVER_BME680_PSON80P300X300X100-8N
SJ1: SJ
TP1, TP2, TP3, TP4, TP5, TP6, TP7, TP8, TP9, TP10, TP11, TP12, TP13, TP14, TP15, TP16, TP17: TPTP20R; TP20R
U1: W25Q512JVEIQ; SON127P600X800X80-9N
U2: ESP32-C6-WROOM-1-N8; XCVR_ESP32-C6-WROOM-1-N8
U3: DS3231SN#; SOIC127P1032X265-16N
U4: MAX17048G+T10; SON50P200X200X80-9N

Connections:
3V3: C1_BAT2.1, C3.+, C9.1, D7.2 (ANODE), IC1.2 (VDD), IC4.5 (VOUT), J3.2, J4.P4 (VDD), Q2.3 (D), R1.1, R1_PINH1.2, R2-PINH1.2, R5.2, R6.2, R7.2, R8.2, R9.2, R10.2, R_BOOT.1, R_CHANGE.1, R_CL1.1, R_RESET.1, TP16.TP, U1.3 (!WP!(IO2)), U1.7 (!HOLD!/!RESET!(IO3)), U1.8 (VCC), U2.2 (3V3), U3.2 (VCC)
32KHZ: R2-PINH1.1, U2.9 (IO1), U3.1 (32KHZ)
DN: D1.4 (I/O2_2), J2.A7, J2.B7
DP: D1.6 (I/O1_2), J2.A6, J2.B6
EPD_3V3: C7.1, EPD_C5.1, J1.15, J1.16, L1.2, Q2.2 (S), TP17.TP
EPD_3V3_C: Q2.1 (G), R_CL1.2, TP13.TP, U2.18 (IO20)
EPD_BUSY: J1.9, TP9.TP, U2.26 (IO3)
EPD_CS: D6.2, J1.12, R9.1, TP10.TP, U2.11 (IO10)
EPD_DC: J1.11, TP11.TP, U2.5 (IO5)
EPD_RST: J1.10, TP12.TP, U2.21 (IO23)
FLASH_CS: D9.2, R5.1, U1.1 (!CS), U2.12 (IO11)
GDR: J1.2, Q3.1 (G), R4.1
GND: BOOT_BUTTON.1, BOOT_BUTTON.2, C1.2, C1_BAT.2, C1_BAT1.2, C1_BAT2.2, C2.2, C2_BAT.2, C3.-, C4_USB.2, C5.2, C5_USB.2, C6.2, C7.2, C8.2, C9.2, C10.2, C10_SUPERCAP.1, CHANGE_BUTTON.1, CHANGE_BUTTON.2, C_DELAY.2, D1.2 (GND), D3.1 (K), D6.1, D8.1, D9.1, D10.1, D11.1, D12.1, EPD_C1.2, EPD_C2.2, EPD_C5.2, EPD_C6.2, EPD_C7.2, EPD_C8.2, EPD_C9.2, EPD_C10.2, EPD_C11.2, EPD_C12.2, IC1.3 (GND), IC4.2 (VSS), J1.8, J1.17, J1.MP1, J1.MP2, J2.A1, J2.A12, J2.B1, J2.B12, J2.MP1, J2.MP2, J2.MP3, J2.MP4, J3.1, J4.G1 (GND_1), J4.G2 (GND_2), J4.G3 (GND_3), J4.G4 (GND_4), J4.P6 (VSS), MCP73831.2 (VSS), R1_PWRUSB.1, R2.1, R2-USB.2, R2-USB1.1, R2_BAT.1, R4.2, RESET_BUTTON.1, RESET_BUTTON.2, SENSOR2.1 (GND), SENSOR2.5 (SDO), SENSOR2.7 (GND), SJ1.1, TP4.TP, TP5.TP, U1.4 (GND), U1.9 (EXP), U2.1 (GND), U2.28 (GND), U2.29_1 (GND), U2.29_2 (GND), U2.29_3 (GND), U2.29_4 (GND), U2.29_5 (GND), U2.29_6 (GND), U2.29_7 (GND), U2.29_8 (GND), U2.29_9 (GND), U3.13 (GND), U4.1 (CTG), U4.4 (GND), U4.6 (QSTRT), U4.9 (EP)
GPIO8: R1.2, U2.10 (IO8)
I2C_PW: C1.1, C2.1, R1_PINH.2, R2-PINH.2, SENSOR2.2 (CSB), SENSOR2.6 (VDDIO), SENSOR2.8 (VDD), U2.17 (IO19)
INT_RTC: R1_PINH1.1, TP15.TP, U2.8 (IO0), U3.3 (SQW/!INT)
IO/BOOT: BOOT_BUTTON.3, BOOT_BUTTON.4, C6.1, R_BOOT.2, U2.15 (IO9)
IO/CHANGE: C10.1, CHANGE_BUTTON.3, CHANGE_BUTTON.4, R_CHANGE.2, U2.23 (IO15)
MISO: D12.2, J4.P7 (DAT0), R8.1, TP6.TP, U1.2 (DO(IO1)), U2.27 (IO2)
MOSI: D11.2, J1.14, J4.P3 (CMD), R7.1, TP7.TP, U1.5 (DI(IO0)), U2.7 (IO7)
unnamed: D7.1 (CATHODE), R_CAPACITOR.2
unnamed: C_DELAY.1, IC1.5 (CT)
unnamed: MCP73831.5 (PROG), R2_BAT.2
unnamed: C4.1, D3.2 (A), D4.1 (K)
unnamed: C1_BAT1.1, D2.1 (CATHODE), IC4.1 (VIN), IC4.3 (CE), Q1.2 (S)
unnamed: MCP73831.1 (STAT), R1_BAT.1
unnamed: CHG_LED.C, R1_BAT.2
unnamed: EPD_C1.1, J1.4
unnamed: EPD_C2.1, J1.5
unnamed: EPD_C6.1, J1.18
unnamed: EPD_C7.1, J1.19
unnamed: EPD_C8.1, J1.20
unnamed: EPD_C10.1, J1.22
unnamed: EPD_C12.1, J1.24
unnamed: J2.A5, R2-USB1.2
unnamed: J2.B5, R2-USB.1
PREVGH: D5.1 (K), EPD_C9.1, J1.21
PREVGL: D4.2 (A), EPD_C11.1, J1.23
RESE: J1.3, Q3.2 (S), R3.1
RESE': R2.2, R3.2, SJ1.2
RESET: C5.1, IC1.1 (VOUT), RESET_BUTTON.3, RESET_BUTTON.4, R_RESET.2, U2.3 (EN)
RTC_RST: U2.16 (IO18), U3.4 (!RST)
RX: TP2.TP, U2.24 (RXD0/GPIO17)
SCK: D10.2, J1.13, J4.P5 (CLK), R6.1, TP8.TP, U1.6 (CLK), U2.6 (IO6)
SCL: J3.4, R2-PINH.1, SENSOR2.4 (SCK), U2.20 (IO22), U3.16 (SCL), U4.7 (SCL)
SDA: J3.3, R1_PINH.1, SENSOR2.3 (SDI), U2.19 (IO21), U3.15 (SDA), U4.8 (SDA)
SRC: C4.2, D5.2 (A), L1.1, Q3.3 (D)
SS_SD: D8.2, J4.P2 (CD/DAT3), R10.1, U2.4 (IO4)
TX: TP1.TP, U2.25 (TXD0/GPIO16)
USB_D+: D1.1 (I/O1_1), U2.14 (IO13)
USB_D-: D1.3 (I/O2_1), U2.13 (IO12)
VBAT: C2_BAT.1, MCP73831.3 (VBAT), Q1.3 (D), TP3.TP, U4.2 (CELL), U4.3 (VDD)
VBUS: C1_BAT.1, C4_USB.1, C5_USB.1, CHG_LED.A, D1.5 (VBUS), D2.2 (ANODE), MCP73831.4 (VIN), PFMF.050.1.2, Q1.1 (G), R1_PWRUSB.2, TP14.TP
VRTC: C8.1, C10_SUPERCAP.2, R_CAPACITOR.1, U3.14 (VBAT)
VUSB: J2.A4, J2.A9, J2.B4, J2.B9, PFMF.050.1.1

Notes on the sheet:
USB C connector & ESD protection
LDO Voltage Regulator
Display Type Selector
E-Paper Drive Circuit
Li-Po Battery Charging Controller
ESP32 C6
SD Card
E-Paper Display Header
EPD Power
Environmental Sensor BME688
Voltage Supervisor + Reset & Boot / IO Button
Battery Charge Level
External NOR Flash 64MB
SPI ESD Protection Lines
Qwiic / Stemma QT
Test Pads
RTC Module DS3231SN
OpenBook Schematic
Popescu Cristian-Emanuel

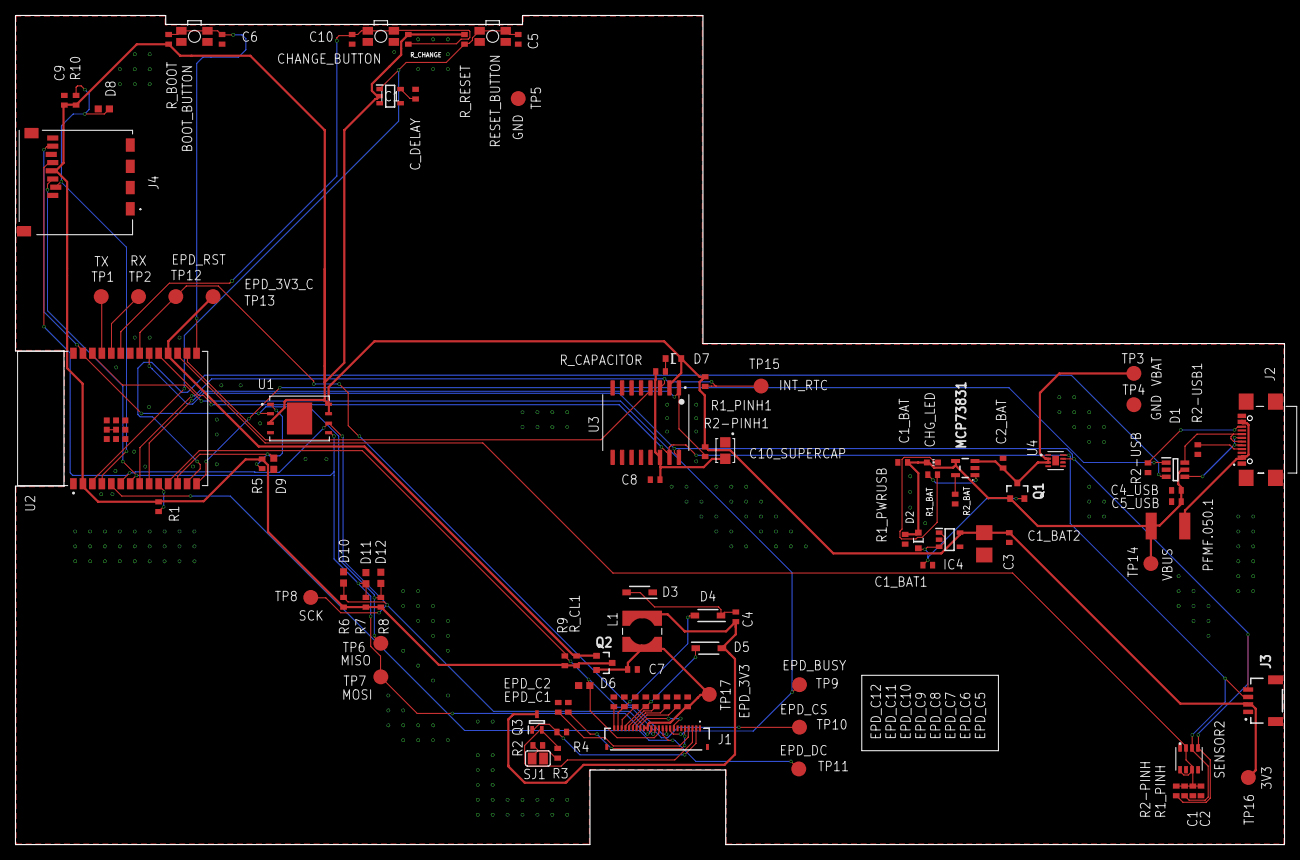
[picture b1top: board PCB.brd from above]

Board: 2 copper layers, 170.2 x 111.2 mm, 103 parts (0 on the bottom side), 55 nets.

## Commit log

2025-04-06 Added final project
2025-04-06 Create LICENSE
2025-04-06 Added README.md
2025-04-06 Updated images
2025-04-06 Updated image
2025-04-11 Fixed issues

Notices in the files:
parts and their libraries:
COPYRIGHT: Copyright (C) 2024 Ultra Librarian. All rights reserved.
